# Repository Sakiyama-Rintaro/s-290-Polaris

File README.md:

# S-290 Polaris 電装システム

## はじめに
初めまして。芝浦工業大学理工学研究科電気電子情報学専攻M1の先山倫太郎です。学部時代の学科は工学部電子工学科です。私は学部時代に鳥人間部に所属していて人力飛行機の製作を行っていました。そこでは電装班と呼ばれる機体のシステム系の開発を行なっている班に所属していて、機体の操舵システムと、高度計などの計測器のシステム開発を行っていました。その詳細についてここでは述べさせていただきます。元々プログラミングに興味があり、何かヒントが得られるのではと思い電装班に入った次第です。<br>
<br>
<br>
このリポジトリでは、**人力飛行機電装システム**において<br>
・Mainプリント基板設計・製作<br>
・計測システム・ソフトウェア設計・製作<br>
・操舵システム・ソフトウェア設計・製作<br>
・各種試験系(回転試験・ER試験・全体接合・TF)<br>
に関することが詰まっています。<br>
<br>

なお、フライトデータ表示用のアプリ開発については次のリポジトリを参考にしてください。Androidアプリ開発、Webアプリ開発やその運用方法について記述してあります。<br>
https://github.com/Sakiyama-Rintaro/FlightDisplay.S290<br>

## 後輩の皆さんへ
我々23代電装班では、「同期や後輩の為にしっかりと技術資料を残す」という方針で活動していました。それは、教え合いの文化を形成し効率的な技術力アップを図るためであったり、悲願の鳥コン出場を達成した代なのでこの文化はぜひ引き継いでいったほしいなと思っています。僕からの願いです。<br>
モノづくりを楽しんで、充実した大学生活を送ってください！！<br>

## リポジトリの説明
**・[TBT_S-290_Polaris_System](https://github.com/Sakiyama-Rintaro/s-290-Polaris/tree/main/Module)** //完成品が入っています。プログラム書き込み方法と基板の取り扱いについては、このリポジトリのREADMEを参考にしてください。<br>
**・[Module](https://github.com/Sakiyama-Rintaro/s-290-Polaris/tree/main/Module)** //単体テストで用いたものが入っています。<br>
**・[Yosan](https://github.com/Sakiyama-Rintaro/s-290-Polaris/tree/main/Yosan)** //S-290での購入品についてのデータが入っています。<br>
**・[doc](https://github.com/Sakiyama-Rintaro/s-290-Polaris/tree/main/doc)** //作ったシステムの写真や動画などが入っています。<br>

## 目次
・はじめに<br>
・ソフトウェア・ハードウェア設計ガイド<br>

## 使ったソフト
・GitHub Desktop (GitHub操作用)<br>
・Visual Studio Code (テキストエディタ mbedのコードを書くときに使います)<br>
・LPCISP.exe (lpc1114にプログラムを書きこむときに使います。後で詳細を説明します)<br>
・Tera Term (ターミナル。シリアル通信のデバッグ、Twelite_シリアル通信アプリのモード変更、ER試験等の時に使います<br>
・Realterm (ターミナル。2進数や16進数のデータの確認に使います。Twelite_シリアル通信アプリ_バイナリモード)<br>
・Google Earth Pro (GPSデータのチェックに使います)<br>
・Android Studio (Androidアプリ開発に使います)<br>
・Autodesk Fusion360 (3DCAD。機速計をはじめとする筐体設計に使用します)<br>
・Autodesk Inventor (3DCAD。機速計をはじめとする筐体設計に使用します)<br>
・AutoCAD Mechanical (2DCAD。3DCADだと寸法が確認しづらいので、確認用にこっちも使います。検図チェックお願いします( ﾟДﾟ))<br>
・EAGLE (回路設計CAD。Main基板の設計に使用します。後で詳細を説明します)<br>

## 使用言語
・C/C++ (mbedで使った)<br>
・Kotlin (Androidアプリ開発で使った)<br>

## 使用マイコン(※主要部のみ)
・mbed LPC1768<br>
・mbed LPC1114<br>

# システム全体図
S-290 Malus電装システムの全体図を示します。<br>
各矢印については、<br>
・黒色: シリアル通信(有線) <br>
・緑色: デジタル通信(有線) <br>
・黄色: Zigbee通信(有線) <br>
・赤色: Bluetooth通信(無線) <br>
・青色: モバイルデータ通信(無線) <br>
となっています。<br>
矢印の方向にデータが飛んでいます。<br>
### システム全体図_その1

### システム全体図_その2

## 各計器・部品等の役割
|計器・部品名|役割|
|---|---|
|[機速計](https://github.com/Sakiyama-Rintaro/s-290-Polaris/blob/main/Module/Airspeed_meter/README.md)|機体の速度(空気に対する相対速度)を計測する|
|[回転数計](https://github.com/Sakiyama-Rintaro/s-290-Polaris/blob/main/doc/picture/Cadence_meter.md)|パイロット達がペダルを回す速さを計測する|
|[高度計](https://github.com/Sakiyama-Rintaro/s-290-Polaris/blob/main/doc/picture/Altimeter.md)|機体の高度を計測する|
|姿勢角計|機体の姿勢情報を計測する|
|心拍計|フライト時におけるパイロット達の心拍数を計測する|
|温度計|サーボモータ付近の温度を計測する|
|[GPS](https://github.com/Sakiyama-Rintaro/s-290-Polaris/blob/main/doc/picture/GPS.md)|機体の現在位置を計測する|
|SD|機速・回転数・高度・姿勢・心拍数・温度・GPS・舵角等の情報を記録する|
|音システム|機体の高度情報を音で知らせる|
|[舵角計](https://github.com/Sakiyama-Rintaro/s-290-Polaris?tab=readme-ov-file)|ER(サーボモータ)の制御角度を表示する|
|[Android端末](https://github.com/Sakiyama-Rintaro/s-290-Polaris/blob/main/doc/picture/Android.md)|前部パイロットにフライト情報を表示する|
|[OLED](https://github.com/Sakiyama-Rintaro/s-290-Polaris0/blob/main/doc/picture/OLED.md)|後部パイロットにフライト情報を表示する|
|Li-Poバッテリー電圧監視システム|サーボモータ用Li-Poバッテリーの残り電圧の情報を記録する|

## システムの設計方針
S-290のシステムでは、無線モジュールtweliteを多用し計測系統の多機能化とパイロット安全の充実化を目指しました。<br>

## S-250からの変更点
・姿勢角計の導入<br>
・心拍計(前部P・後部P)の導入<br>
・温度計の導入<br>
・Li-poバッテリー電源監視システムの導入<br>
・フライト監視システムの導入<br>
・自作出力計の廃止と市販出力計Germin Vector3の導入<br>
・Mainプリント基板の実装部品の変更<br>
・操舵方式の変更<br>
となっています。

## 本システムの良かった点
・無線モジュールを使って、計測システムの多機能化が出来た点<br>
・無線モジュールを使って、接合時間の短縮を目指せた点<br>
・Li-Poバッテリー電圧監視システムにより、パイロット安全が向上した点(現在製作中)<br>

## 本システムの悪かった点
・無線モジュールを沢山使用したことにより、コストが大きくなってしまった点<br>
・表面実装部品の採用により、ハードウェア製作難易度が高い点<br>

# システムの詳細
## 通信方式
本システムで採用しているマイコンのlpc1768とlpc1114では、シリアル通信方式として、UART(通信)、SPI(通信)、I2C(通信)があります。<br>
S-290電装システムにおいて、すべてのシリアル通信によるデータ通信は、UART(通信)のみを使用しました(姿勢角計を除く)。<br>
<br>
<各種計器の設計・製作の観点での理由><br>
コストや製作期間の都合上、各種計器はユニバーサル基板を使って作るのですが、このユニバーサル基板はプリント基板よりもノイズが発生しやすいです。故に、同期式通信でノイズに弱いSPIとI2Cよりもリカバリーが効きやすいUARTを採用しました。<br>
<br>
<Mainプリント基板の設計・製作の観点での理由><br>
配線数が増えて面倒だと思ったため。<br>

## 有線と無線の使い分け
S-290は、有線と無線を組み合わせたシステムとなっています。<br>
人力飛行機の電装システムにおける有線と無線のメリット・デメリットをそれぞれ挙げた後、各計器・部品での採用方式について説明します。<br>
<br>
<有線 メリット><br>
・安定した通信ができる<br>
<有線 デメリット><br>
・配線が必要なため、TFや全体接合等の試験系における接合時間が長くなってしまう<br>
<br>
<無線 メリット><br>
・接合時間を短縮できる<br>
<無線 デメリット><br>
・障害物などの影響で安定しないことがある<br>
・コストが上がる<br>
<br>
|計器・部品名|有線 or 無線|採用理由|
|---|---|---|
|[機速計](https://github.com/Ryosuke-123/doritos.tbt.denso.21st/blob/main/doc/picture/Airspeed_meter.md)|無線|接合時間短縮のため|
|[回転数計](https://github.com/Ryosuke-123/doritos.tbt.denso.21st/blob/main/doc/picture/Cadence_meter.md)|無線|接合時間短縮のため|
|[高度計](https://github.com/Ryosuke-123/doritos.tbt.denso.21st/blob/main/doc/picture/Altimeter.md)|有線|コスト削減のため|
|姿勢角計|無線|接合時間短縮のため|
|心拍計|無線|接合時間短縮のため|
|温度計|無線|接合時間短縮のため|
|[舵角計](https://github.com/Ryosuke-123/doritos.tbt.denso.21st/blob/main/doc/picture/Rudder_Angle_meter.md)|有線|通信の信頼性を上げるため|
|[GPS](https://github.com/Ryosuke-123/doritos.tbt.denso.21st/blob/main/doc/picture/GPS.md)|有線|コスト削減のため|
|SD|有線|プリント基板上に乗せられるほどの余裕があったため|
|スピーカー(音システム)|有線||
|[Android端末](https://github.com/Ryosuke-123/doritos.tbt.denso.21st/blob/main/doc/picture/Android.md)|有線|通信の信頼性を上げるため|
|[OLED](https://github.com/Ryosuke-123/doritos.tbt.denso.21st/blob/main/doc/picture/OLED.md)|有線|通信の信頼性を上げるため|
|サーボモータ|有線|通信の信頼性を上げるため|
|ジョイスティック(操縦桿)|有線|通信の信頼性を上げるため|
|Li-Poバッテリー電圧監視システム|無線|接合時間短縮のため|

## 操舵系統に不具合を起こさない設計
パイロットの命が関わる操舵系統で、トラブルが起こらないように設計しました。<br>
具体的には、操舵用マイコンには他のマイコンからデータを送り付けないようにし、データ処理が追い付かず操舵に影響が出ないようにしました。

## パイロット達が安全措置を行える設計
Android端末、OLED、音システム、舵角計、リポバッテリー電圧監視システムを採用し、パイロットや併走艇に乗る全体設計者が機体の状況を常に把握できるようにしました。

## 前部P用表示器と後部P用表示器に映す情報の使い分け
TBTの機体は、他チームの機体と異なり2人乗りです。つまりパイロットが2人居るということです。<br>
実際の航空機において機長と副操縦士が操縦とフライト情報のモニタリングを分けて行うように、TBTのパイロット達にも役割分担をさせましょう。1人で処理できる情報には限りがありますからね( ﾟДﾟ)。<br>
S-290では、以下のようにしました。<br>
<br>
<前部パイロット><br>
操縦優先。舵角計や高度情報などフライト操縦に必要な情報のみを表示。進路方向や風向きの状況判断など、意思決定権を持つ。<br>
視界が見えやすく、操縦悍を持っているため基本的には漕ぎながら操縦に集中してもらう。<br>
<br>
<後部パイロット><br>
表示確認→全部パイロットへ伝達を担当。また後部のみアップライト型なのでとにかく出力を出して前部パイロットを支援する。<br>
全体的に前部パイロットの補佐の役割を担う。<br>
<br>
# 設計に関する勉強について

## 電装設計&責任者の年間スケジュールについて
S-290では、コロナによる学内活動禁止が繰り返し行われたため、製作スケジュールに大きな影響をもたらしました。(別の要因もありましたが...)<br>
以下に、僕の当初の活動予定と実際の活動状況について示した表を示します。今後の参考にしてください。<br>

|月|予定|記録|
|---|---|---|
|8月|ひたすら勉強、TP(テストピース)作成、運営陣会議|新入生集め|
|9月|P選考、勉強、TP作成|勉強、TP作成、新入生集め、活動方針決定、運営陣会議|
|10月|勉強、TP作成|勉強、TP作成、P選考|
|11月|勉強、TP作成|勉強、TP作成|
|12月|マザボプロトタイプ製作、プリント基板発注|勉強、TP作成|
|1月|Main基板部品実装・ソフトウェア作成、鳥コン書類執筆|勉強、TP作成|
|2月|マザボほぼ完成、CF三昧、利根川精工にサーボ発注|マザボプロトタイプ製作、プリント基板発注|
|3月|マザボ調整・各種計器作成|プリント基板再発注、CF三昧|
|4月|全体接合・回転試験・ER試験準備、マザボ調整|Main基板部品実装・ソフトウェア作成、CF三昧|
|5月|全体接合・回転試験・ER試験準備、マザボ調整|マザボほぼ作成、各種計器作成|
|6月|TF、マザボ調整|TF,マザボ調整||
|7月|TF、鳥コン|TF、鳥コン||

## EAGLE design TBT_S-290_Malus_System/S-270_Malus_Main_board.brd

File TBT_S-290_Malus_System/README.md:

## はじめに
S-270 Malus電装システムにおけるMain基板のシステムを再現するために必要なことが書かれています。参考にしてください。<br>

## 各ファイルについて
・S-270_Malus_board.zip : Fusion PCBにて発注するデータ<br>
・S-270_Malus_Main_board.sch : メイン基板回路図<br>
・S-270_Malus_Main_board.brd : メイン基板配線図<br>
・S-270_Malus_Main_board_sch.png : メイン基板回路図写真<br>
・S-270_Malus_Main_board_brd.png : メイン基板配線図写真<br>
・S-270_Malus_board_parts : プリント基板に使った部品一覧 <br>
・Android_System_for_test : Androidプログラム。数字表示するだけ<br>
・S-270_main_lpc1768.cpp : 計測用マイコンプログラム<br>
・S-270_ER_lpc1768.cpp : 操舵用マイコンプログラム<br>
・S-270_twe_lpc1114.cpp : 無線モジュール用マイコンプログラム<br>
・S-270_gps_lpc1114.cpp : GPS用マイコンプログラム<br>
・S-270_sound_lpc1114.cpp : 音システム用マイコンプログラム<br>
・S-270_airspeed_meter_lpc1114 : 対気速度計用マイコンプログラム(送信機)<br>
・S-270_cadence_meter_lpc1114 : 回転数計用マイコンプログラム(送信機)<br>

## 目次
・基板準備<br>
・部品実装<br>
・自作書き込み機の準備<br>
・書き込みソフトウェアの準備<br>

## 基板準備
### Step1
リポジトリから「S-270_Malus_board.zipファイル」をダウンロードする。<br>

### Step2
Fusion PCBのサイト[(Click Here)](https://www.fusionpcb.jp/fusion_pcb.html)に行き、ダウンロードしたzipファイルをアップロードする。<br>
  (設定) <br>
  ・材質: FR-4 TG130 <br>
  ・層数: 二層 <br>
  ・寸法: 80.0 * 100.0 <br>
  ・製造枚数: 好きな枚数 <br>
  ・異種面付けの種類: 1 <br>
  ・板厚: 1.60 <br>
  ・レジスト色: 好きな色 <br>
  ・基板の表面処理: HASL(有鉛半田レベラー) <br>
  ・最小ソルダレジストダムの幅: 0.4mm↑ <br>
  ・銅箔厚: 1oz. <br>
  ・最小穴径: 0.3mm <br>
  ・最小パターン幅/パターン間隔: 6/6 mil <br>
  ・端面スルーホール: なし <br>
  ・インピーダンス制御: なし <br>
  
### Step3
ページの指示に従って、発注をかける。<br>

## 部品実装
届いた基板に部品を実装しましょう。<br>
使用する部品は、「S-270_Malus_board_parts.xlsx」に記載されています。<br>

## 自作書き込み機の準備
### lpc1114FDH28(表面実装版lpc1114)用書き込み機
S-270で使った書き込み機の写真とその回路配線についての写真を下に示します。<br>
<写真><br>

<回路図><br>

### 表面実装版twelite用書き込み機
S-270で使った書き込み機の写真とその回路配線についての写真を下に示します。<br>
<写真><br>

<回路図><br>

## 書き込み用ソフトウェアの準備
lpc1114FDH28とtweliteへのプログラム書き込みには、それぞれ専用のソフトウェアが必要です。<br>
まずは、必要なソフトウェアをダウンロードしましょう。<br>
<br>
・LPCISP.exe(lpc1114FDH28への書き込みに必要) [Click!](https://synapse.kyoto/tips/LPC1114/page002.html)<br>
・TWE-Programmer.exe(tweliteへの書き込みに必要) [Click!](https://mono-wireless.com/jp/products/TWE-APPS/LiteProg/index.html)<br>
・Tera Term(tweliteに書き込む「シリアル通信アプリ」のターミナル設定に必要) [Click!](https://forest.watch.impress.co.jp/library/software/utf8teraterm/)<br>
<br>

### lpc1114FDH28への書き込み

### tweliteへの書き込みと設定

・Device ID: 0x00<br>
・UART band: 115200<br>
・UART mode: Binary formatted<br>

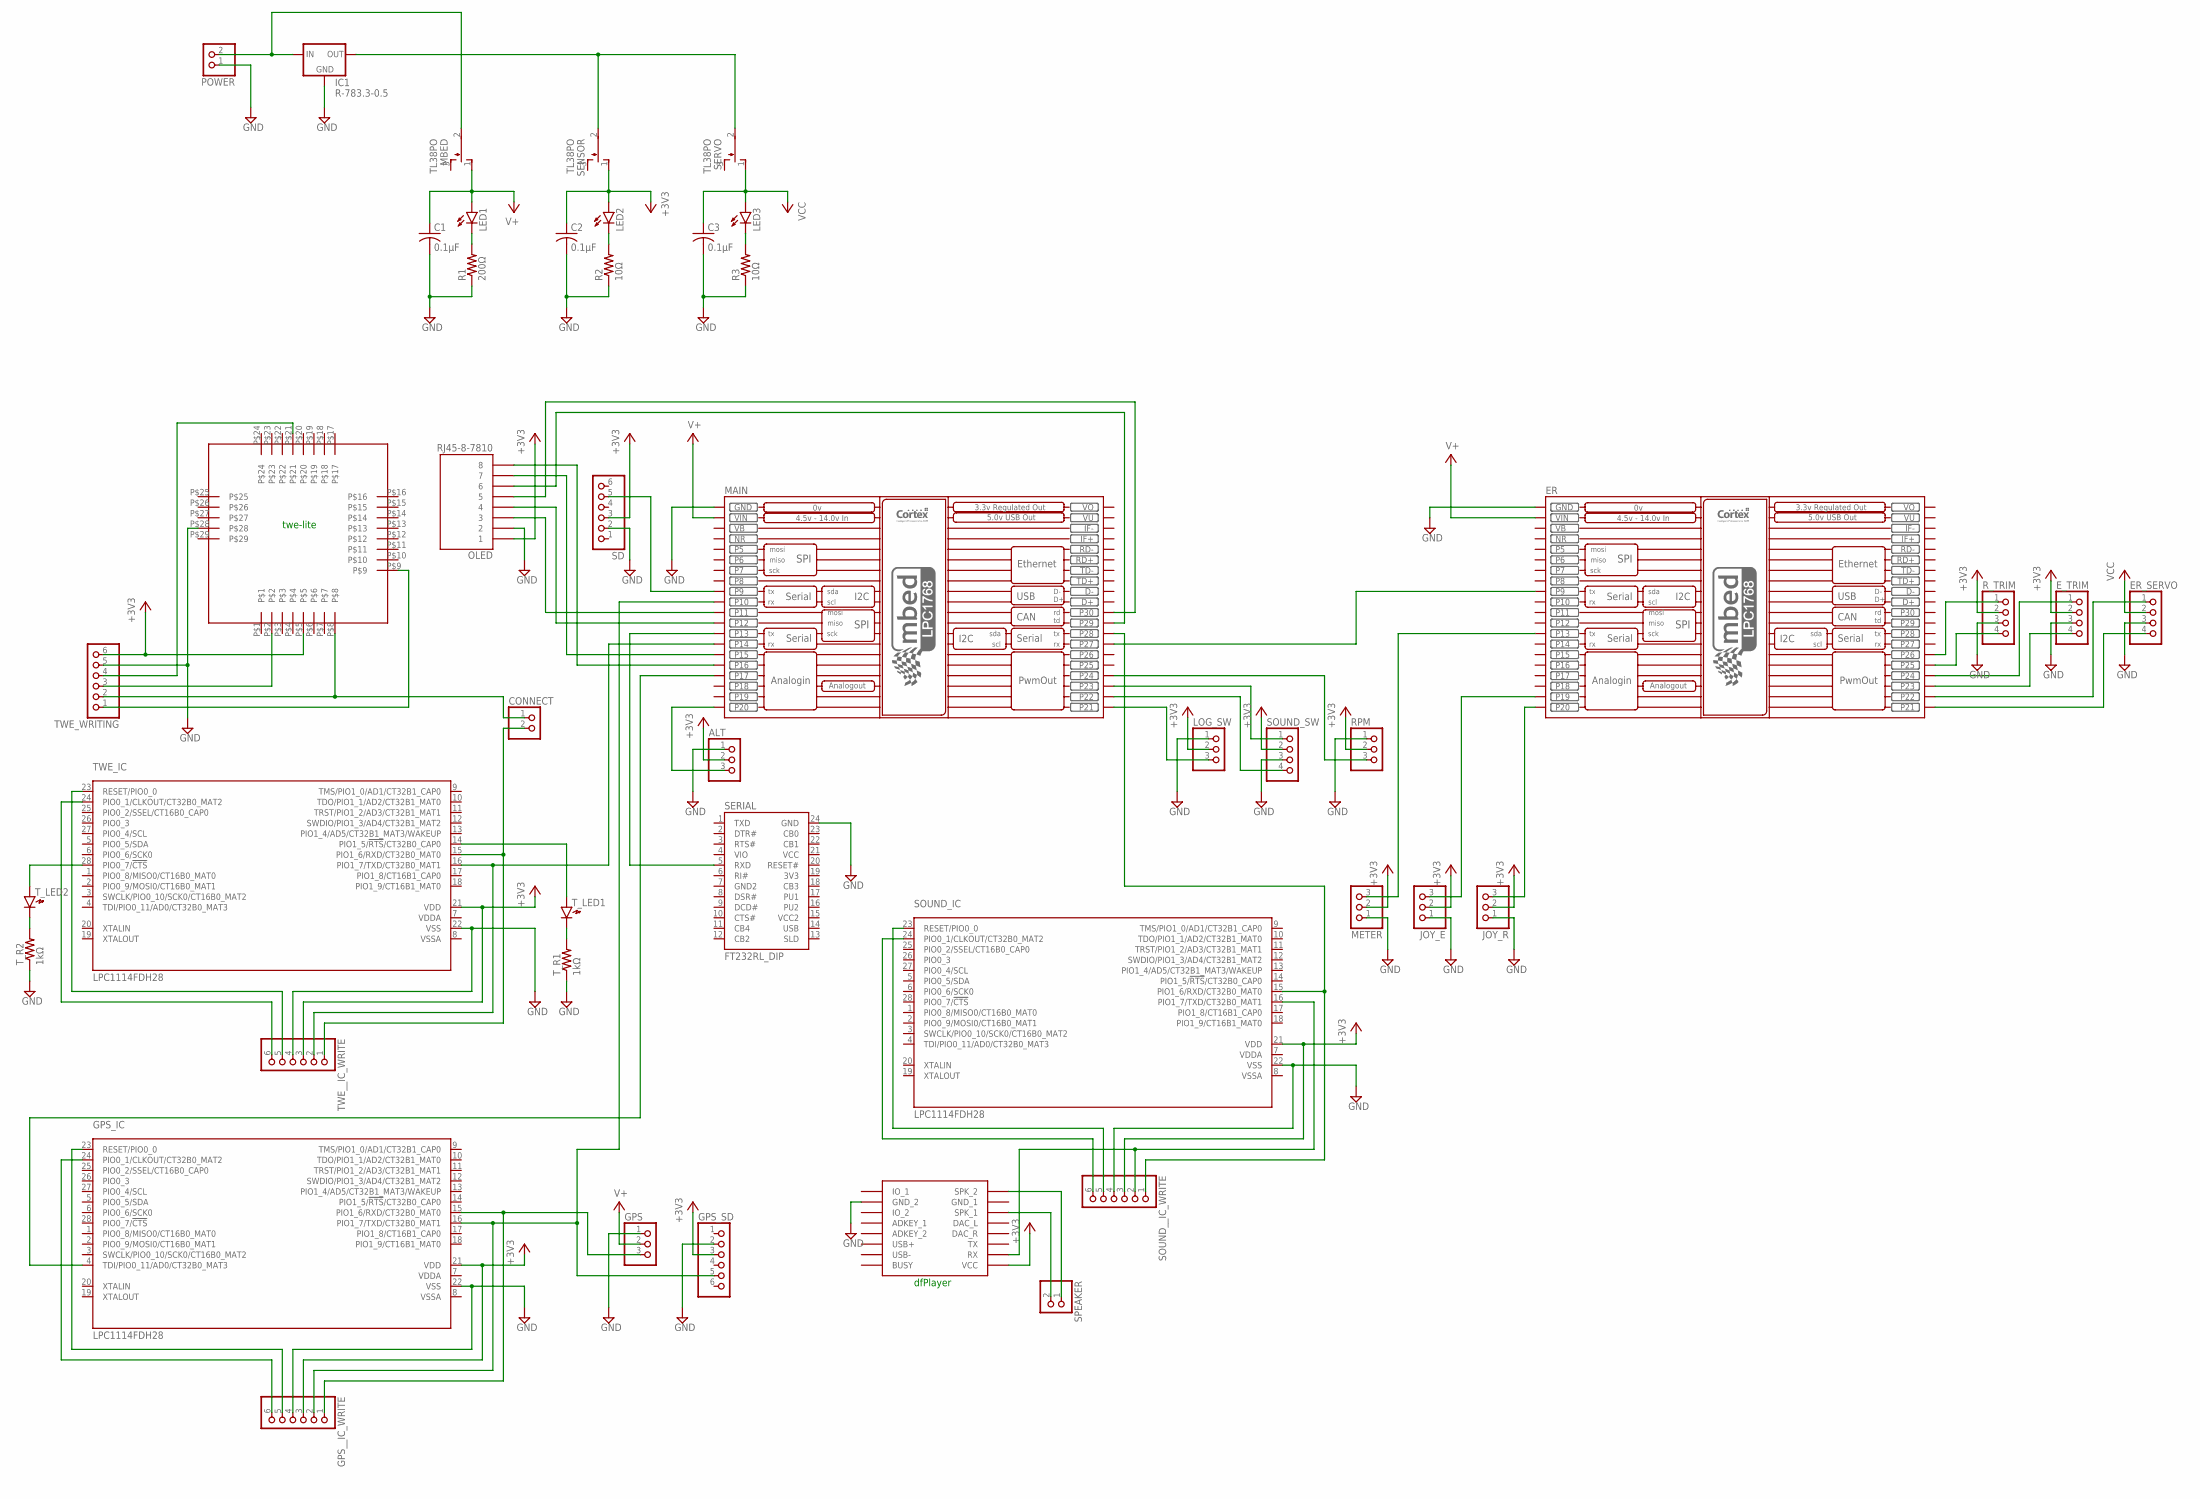
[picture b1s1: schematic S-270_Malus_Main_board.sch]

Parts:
ALT: PINHD-1X3; 1X03
C1, C2, C3: 0.1μF; C0603
CONNECT: PINHD-1X2; 1X02
ER: MBED_NXP_LPC1768; MBED-KIT
ER_SERVO: PINHD-1X4/90; 1X04/90
E_TRIM: PINHD-1X4; 1X04
GPS: PINHD-1X3; 1X03
GPS_IC: LPC1114FDH28; SOT361-1
GPS_SD: PINHD-1X6; 1X06
GPS__IC_WRITE: PINHD-1X6; 1X06
IC1: R-783.3-0.5; SIP3
JOY_E: PINHD-1X3; 1X03
JOY_R: PINHD-1X3; 1X03
LED1, LED2, LED3: LED3MM
LOG_SW: PINHD-1X3; 1X03
MAIN: MBED_NXP_LPC1768; MBED-KIT
MBED: TL38PO; TL3XPO
METER: PINHD-1X3; 1X03
OLED: RJ45-8-7810; RJ-45_7810-8P8C
POWER: PINHD-1X2; 1X02
R1: 200Ω; R0603
R2, R3: 10Ω; R0603
RPM: PINHD-1X3; 1X03
R_TRIM: PINHD-1X4; 1X04
SD: PINHD-1X6; 1X06
SENSOR: TL38PO; TL3XPO
SERIAL: FT232RL_DIP
SERVO: TL38PO; TL3XPO
SOUND_IC: LPC1114FDH28; SOT361-1
SOUND_SW: PINHD-1X4; 1X04
SOUND__IC_WRITE: PINHD-1X6; 1X06
SPEAKER: PINHD-1X2; 1X02
TWE_IC: LPC1114FDH28; SOT361-1
TWE_WRITING: PINHD-1X6; 1X06
TWE__IC_WRITE: PINHD-1X6; 1X06
T_LED1, T_LED2: LED1608
T_R1, T_R2: 1kΩ; R0603
U$1: DFPLAYER
U$2: LITE

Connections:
+3V3: ALT.2, C2.1, E_TRIM.2, GPS_IC.21 (VDD), GPS_SD.3, GPS__IC_WRITE.3, JOY_E.2, JOY_R.2, LED2.A, LOG_SW.2, METER.2, OLED.1, RPM.2, R_TRIM.2, SD.3, SENSOR.1 (O), SOUND_IC.21 (VDD), SOUND_SW.2, SOUND__IC_WRITE.3, TWE_IC.21 (VDD), TWE_WRITING.6, TWE__IC_WRITE.3, U$1.VCC, U$2.P$5
GND: ALT.1, C1.2, C2.2, C3.2, ER.GND, ER_SERVO.3, E_TRIM.3, GPS.1, GPS_IC.22 (VSS), GPS_SD.2, GPS__IC_WRITE.4, IC1.2 (GND), JOY_E.1, JOY_R.1, LOG_SW.1, MAIN.GND, METER.1, OLED.2, POWER.1, R1.1, R2.1, R3.1, RPM.1, R_TRIM.3, SD.2, SERIAL.24 (GND), SOUND_IC.22 (VSS), SOUND_SW.3, SOUND__IC_WRITE.4, TWE_IC.22 (VSS), TWE_WRITING.5, TWE__IC_WRITE.4, T_R1.1, T_R2.1, U$1.GND_2, U$2.P$28
unnamed: IC1.1 (IN), MBED.2, POWER.2
unnamed: LED1.K (C), R1.2
unnamed: LOG_SW.3, MAIN.P$21 (P21)
unnamed: LED3.K (C), R3.2
unnamed: LED2.K (C), R2.2
unnamed: MAIN.P$24 (P24), RPM.3
unnamed: MAIN.P$9 (P9), SD.5
unnamed: IC1.3 (OUT), SENSOR.2, SERVO.2
unnamed: MAIN.P$23 (P23), SOUND_SW.1
unnamed: MAIN.P$11 (P11), OLED.3
unnamed: MAIN.P$22 (P22), SOUND_SW.4
unnamed: MAIN.P$12 (P12), OLED.4
unnamed: MAIN.P$30 (P30), OLED.5
unnamed: MAIN.P$29 (P29), OLED.6
unnamed: MAIN.P$15 (P15), OLED.7
unnamed: MAIN.P$16 (P16), OLED.8
unnamed: GPS_IC.23 (RESET/PIO0_0), GPS__IC_WRITE.5
unnamed: GPS_IC.24 (PIO0_1/CLKOUT/CT32B0_MAT2), GPS__IC_WRITE.6
unnamed: GPS_IC.16 (PIO1_7/TXD/CT32B0_MAT1), GPS_SD.5, GPS__IC_WRITE.2, MAIN.P$10 (P10)
unnamed: GPS.3, GPS_IC.15 (PIO1_6/RXD/CT32B0_MAT0), GPS__IC_WRITE.1
unnamed: SOUND_IC.23 (RESET/PIO0_0), SOUND__IC_WRITE.5
unnamed: SOUND_IC.24 (PIO0_1/CLKOUT/CT32B0_MAT2), SOUND__IC_WRITE.6
unnamed: TWE_IC.23 (RESET/PIO0_0), TWE__IC_WRITE.5
unnamed: TWE_IC.24 (PIO0_1/CLKOUT/CT32B0_MAT2), TWE__IC_WRITE.6
unnamed: SOUND_IC.16 (PIO1_7/TXD/CT32B0_MAT1), SOUND__IC_WRITE.2, U$1.RX
unnamed: MAIN.P$28 (P28), SOUND_IC.15 (PIO1_6/RXD/CT32B0_MAT0), SOUND__IC_WRITE.1
unnamed: MAIN.P$14 (P14), TWE_IC.16 (PIO1_7/TXD/CT32B0_MAT1), TWE__IC_WRITE.2
unnamed: CONNECT.2, TWE_IC.15 (PIO1_6/RXD/CT32B0_MAT0), TWE__IC_WRITE.1
unnamed: TWE_IC.14 (PIO1_5/!RTS!/CT32B0_CAP0), T_LED1.A
unnamed: SPEAKER.2, U$1.SPK1 (SPK_1)
unnamed: SPEAKER.1, U$1.SPK2 (SPK_2)
unnamed: T_LED1.K, T_R1.2
unnamed: TWE_IC.28 (PIO0_7/!CTS!), T_LED2.A
unnamed: T_LED2.K, T_R2.2
unnamed: MAIN.P$13 (P13), SERIAL.5 (RXD)
unnamed: ALT.3, MAIN.P$20 (P20)
unnamed: TWE_WRITING.4, U$2.P$21
unnamed: TWE_WRITING.3, U$2.P$2
unnamed: CONNECT.1, TWE_WRITING.2, U$2.P$8
unnamed: TWE_WRITING.1, U$2.P$9
unnamed: GPS_IC.4 (TDI/PIO0_11/AD0/CT32B0_MAT3), MAIN.P$17 (P17)
unnamed: ER.P$9 (P9), MAIN.P$27 (P27)
unnamed: ER.P$13 (P13), METER.3
unnamed: ER.P$19 (P19), JOY_E.3
unnamed: ER.P$20 (P20), JOY_R.3
unnamed: ER.P$26 (P26), R_TRIM.1
unnamed: ER.P$24 (P24), E_TRIM.1
unnamed: ER.P$25 (P25), R_TRIM.4
unnamed: ER.P$23 (P23), E_TRIM.4
unnamed: ER.P$22 (P22), ER_SERVO.1
unnamed: ER.P$21 (P21), ER_SERVO.4
NR: ER.NR, MAIN.NR
V+: C1.1, ER.VIN, GPS.2, LED1.A, MAIN.VIN, MBED.1 (O)
VB: ER.VB, MAIN.VB
VCC: C3.1, ER_SERVO.2, LED3.A, SERVO.1 (O)
VDDA: GPS_IC.7 (VDDA), SOUND_IC.7 (VDDA), TWE_IC.7 (VDDA)
VO: ER.VOUT (VO), MAIN.VOUT (VO)
VSSA: GPS_IC.8 (VSSA), SOUND_IC.8 (VSSA), TWE_IC.8 (VSSA)
VU: ER.VU, MAIN.VU

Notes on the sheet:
twe-lite
dfPlayer

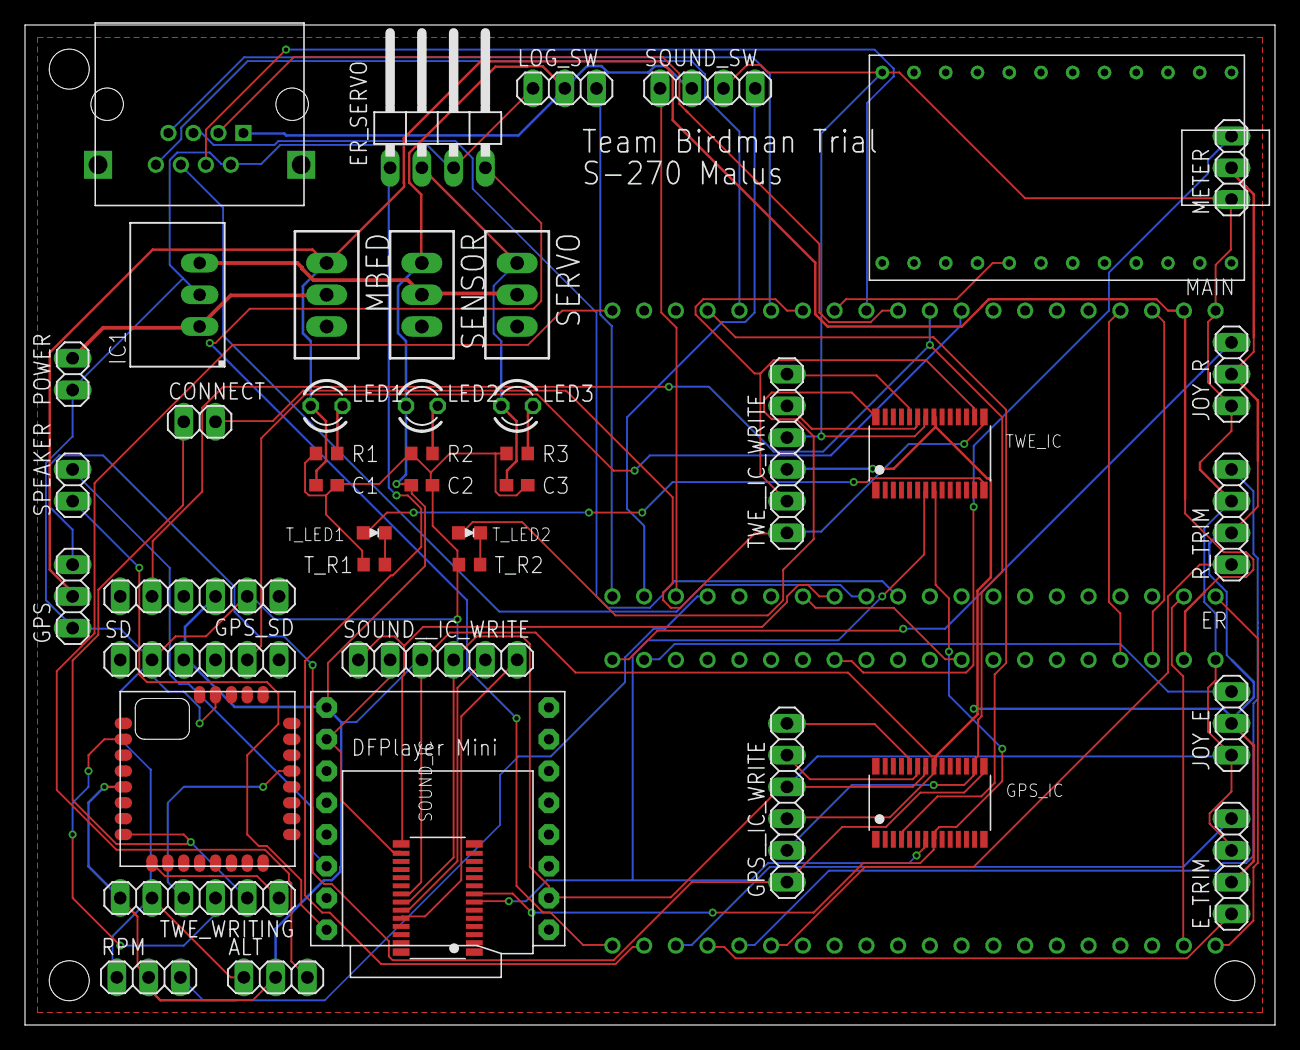
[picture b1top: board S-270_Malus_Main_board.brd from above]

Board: 2 copper layers, 100.0 x 80.0 mm, 46 parts (0 on the bottom side), 61 nets.

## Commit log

2025-10-26 [Add] index
2025-10-26 [Add}index2
2025-10-26 s-290
2025-10-26 Update README to remove outdated references
    Removed references to specific team members and their repositories related to various sensors.
2025-10-28 Fix formatting in README for June and July entries

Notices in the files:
parts and their libraries:
r-78xx_10: (c) 2015 Samuel Lourenço
